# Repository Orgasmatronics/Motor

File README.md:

### Motor

This is a modular system for manufacturing motors scalably from the waste streams of consumer capitalism.   

The system consists of:

1. a control board
2. drive and pickup coils
3. energy storage
4. mechanical-to-electrical energy conversion circuits
4. modular mechanical framing system
5. mechanical oscillators(mass + spring)
6. bearings, shafts and drive trains
7. IoT interface

Taken together, the components of this system should be usable to construct machines that can automate the manufacture of more components of the system, creating the ability to self-propagate.  

As of now(November 2015) there are several parts that have to be either bought or made with commercial tools like the 3d printer.  A ongoing goal of this project is to replace all those components so that the whole project can be re-created from scratch using waste streams _only_.

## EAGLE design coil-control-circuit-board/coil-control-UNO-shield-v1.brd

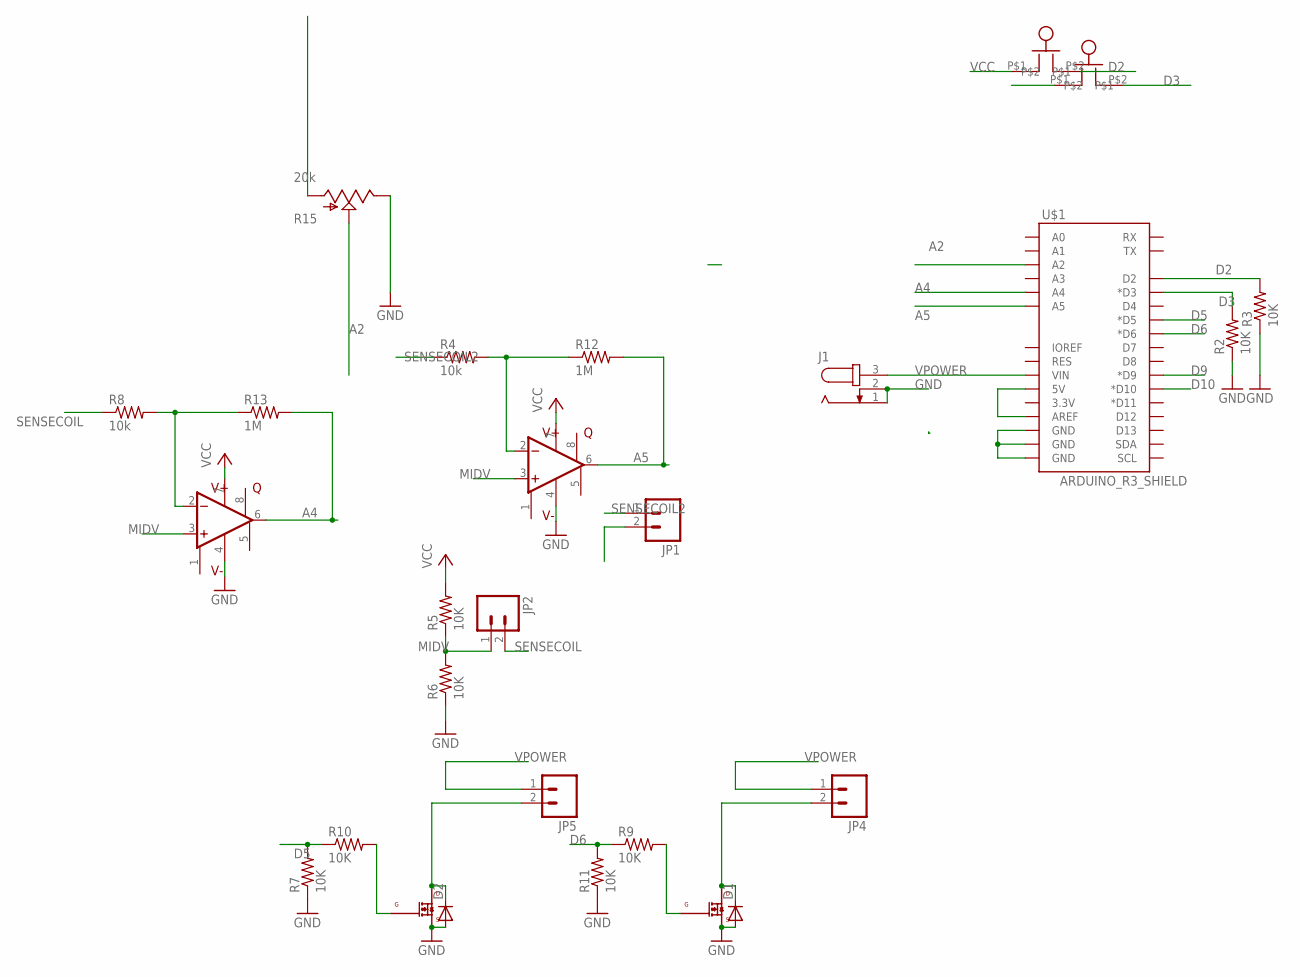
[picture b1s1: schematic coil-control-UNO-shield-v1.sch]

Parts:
D1, D2: DIODE-DO-214AC; DO-214AC
J1: JACK-PLUG1; SPC4078
JP1, JP2, JP4, JP5: M02PTH; 1X02
Q1, Q2: IRLML0060; SOT-23
R2, R3, R5, R6, R7, R9, R10, R11: 10K; R0603
R4, R8: 10k; 0603-RES
R12, R13: 1M; 0805
R15: 20k; ALPS_POT_KIT
SW2, SW3: BUTTON
U2, U3: LM4250; DIP08
U$1: ARDUINO_R3_SHIELD; UNO_R3_SHIELD

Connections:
A2: R15.P$2 (S), U$1.A2
A4: R13.2, U2.6 (OUT), U$1.A4
A5: R12.2, U3.6 (OUT), U$1.A5
D2: R3.2, SW2.P$2, U$1.D2
D3: R2.2, SW3.P$2, U$1.D3 (*D3)
D5: R7.2, R10.1, U$1.D5 (*D5)
D6: R9.1, R11.2, U$1.D6 (*D6)
D9: U$1.D9 (*D9)
D10: U$1.D10 (*D10)
GND: D1.A, D2.A, J1.1, J1.2, Q1.2 (SOURCE), Q2.2 (SOURCE), R2.1, R3.1, R6.1, R7.1, R11.1, R15.P$1 (E), U2.4 (V-), U3.4 (V-), U$1.GND@0 (GND), U$1.GND@1 (GND), U$1.GND@2 (GND)
MIDV: JP1.2, JP2.1, R5.1, R6.2, U2.3 (+IN), U3.3 (+IN)
unnamed: R4.2, R12.1, U3.2 (-IN)
unnamed: Q1.1 (GATE), R9.2
unnamed: R8.2, R13.1, U2.2 (-IN)
unnamed: D1.C, JP4.2, Q1.3 (DRAIN)
unnamed: Q2.1 (GATE), R10.2
unnamed: D2.C, JP5.2, Q2.3 (DRAIN)
SENSECOIL: JP2.2, R8.1
SENSECOIL2: JP1.1, R4.1
VCC: R5.2, R15.P$3 (A), SW2.P$1, SW3.P$1, U2.7 (V+), U3.7 (V+), U$1.5V, U$1.AREF
VPOWER: J1.3, JP4.1, JP5.1, U$1.VIN

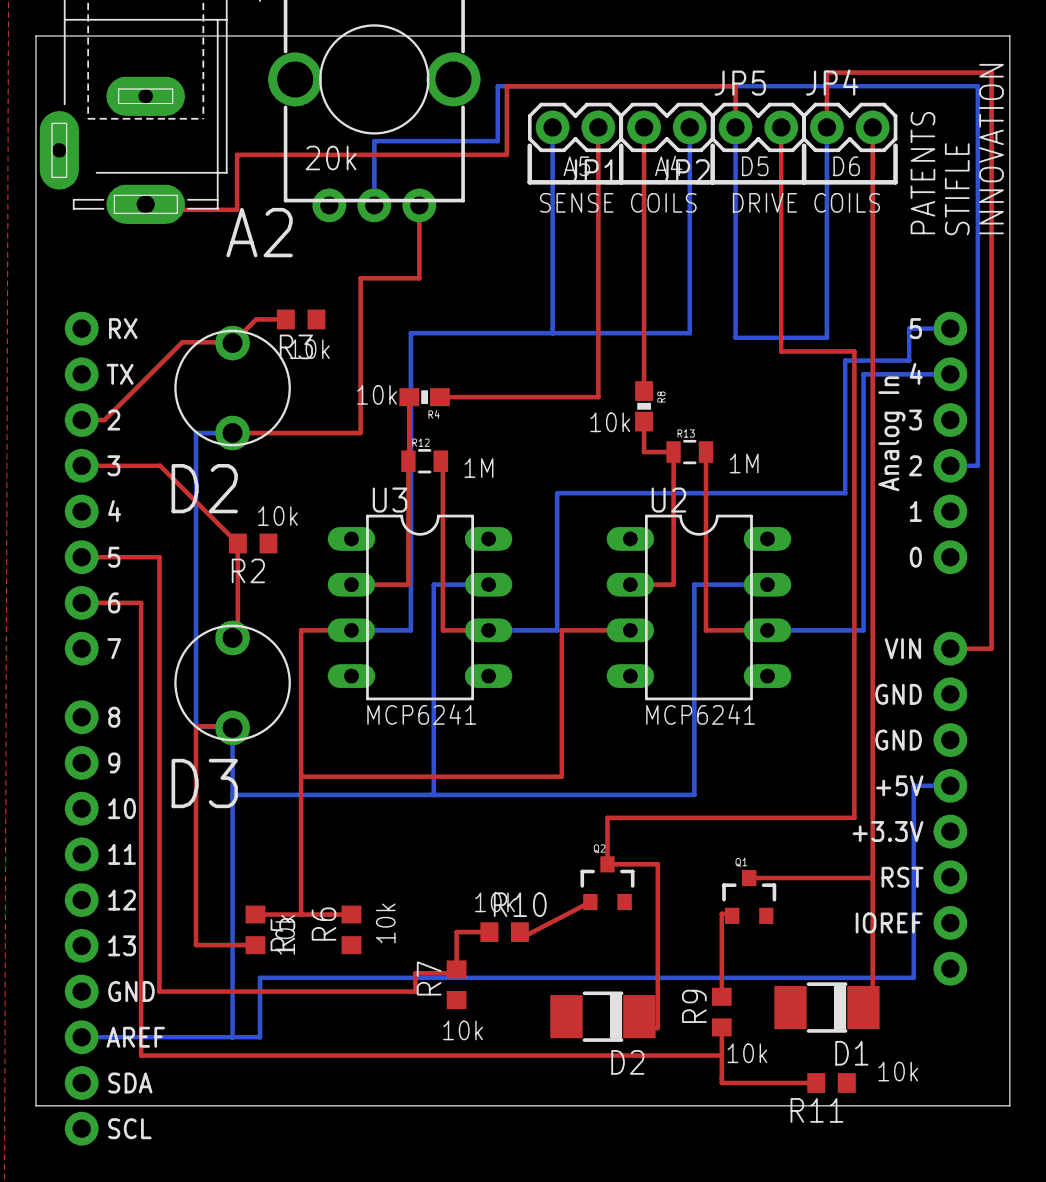
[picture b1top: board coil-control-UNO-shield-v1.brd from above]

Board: 2 copper layers, 54.1 x 59.4 mm, 27 parts (0 on the bottom side), 19 nets.

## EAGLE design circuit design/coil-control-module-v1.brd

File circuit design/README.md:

version 3: assembled fall 2015, used all through october and november

version 4: finishing it up late november, assembly planned soon

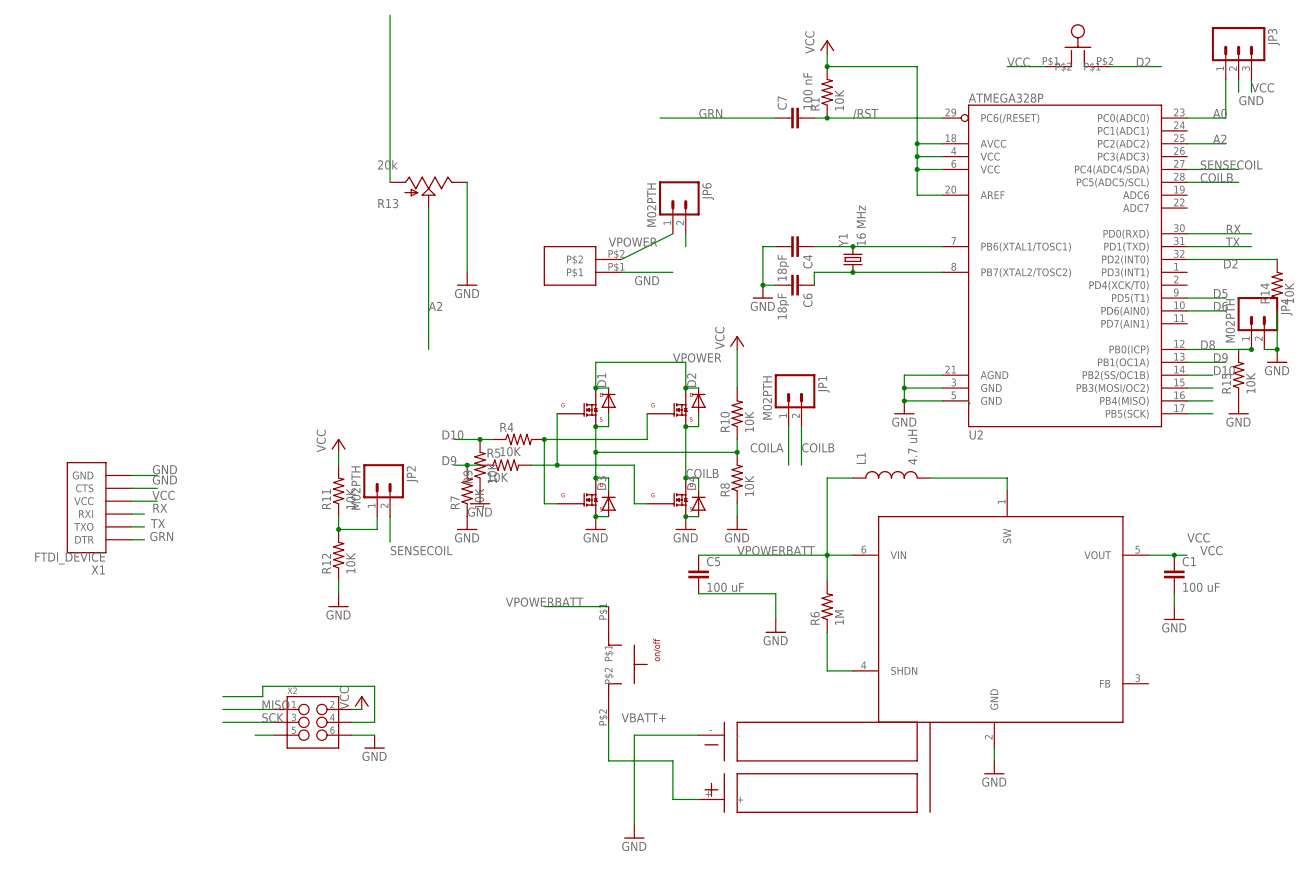
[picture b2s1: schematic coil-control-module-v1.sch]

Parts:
C1, C5: 100 uF; 1206
C4, C6: 18pF; C0603
C7: 100 nF; 0603-CAP
D1, D2, D3, D4: DIODE-DO-214AC; DO-214AC
JP1, JP2, JP4, JP6: M02PTH; 1X02
JP3: M03PTH; 1X03
L1: 4.7 uH; 0805
R1, R4, R5, R7, R8, R9, R10, R11, R12, R14, R15: 10K; R0603
R6: 1M; 0805
R13: 20k; ALPS_POT_KIT
U1: AAT1217; SSOT23-6
U2: ATMEGA328P; TQFP32-08
U$1, U$2, U$3, U$6: IRLML0060; SOT-23
U$4: AA-DOUBLE-UPSIDE-DOWN
U$5: CW182-ND
U$7: BUTTON
U$8: SPRING-TERMINAL
X1: FTDI_DEVICE; FTDI_DEVICE_SIDE
X2: M03X2NO_SILK; 2X3-NS
Y1: 16 MHz; CRYSTAL-SMD-5X3

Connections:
/RST: C7.2, R1.1, U2.29 (PC6(/RESET)), X2.5
A0: JP3.1, U2.23 (PC0(ADC0))
A2: R13.P$2 (S), U2.25 (PC2(ADC2))
COILA: D1.A, D3.C, JP1.1, R8.2, R10.1, U$3.2 (SOURCE), U$6.3 (DRAIN)
COILB: D2.A, D4.C, JP1.2, U2.28 (PC5(ADC5/SCL)), U$1.3 (DRAIN), U$2.2 (SOURCE)
D2: R14.2, U2.32 (PD2(INT0)), U$7.P$2
D5: U2.9 (PD5(T1))
D6: U2.10 (PD6(AIN0))
D8: JP4.1, R15.2, U2.12 (PB0(ICP))
D9: R5.1, R7.2, U2.13 (PB1(OC1A))
D10: R4.1, R9.2, U2.14 (PB2(SS/OC1B))
GND: C1.2, C4.2, C5.2, C6.2, D3.A, D4.A, JP3.2, JP4.2, R7.1, R8.1, R9.1, R12.1, R13.P$1 (E), R14.1, R15.1, U1.2 (GND), U2.3 (GND), U2.5 (GND), U2.21 (AGND), U$1.2 (SOURCE), U$4.-, U$6.2 (SOURCE), U$8.P$1, X1.P$5 (CTS), X1.P$6 (GND), X2.6
GRN: C7.1, X1.P$1 (DTR)
MISO: U2.16 (PB4(MISO)), X2.1
MOSI: U2.15 (PB3(MOSI/OC2)), X2.4
unnamed: C4.1, U2.7 (PB6(XTAL1/TOSC1)), Y1.3 (2)
unnamed: C6.1, U2.8 (PB7(XTAL2/TOSC2)), Y1.1
unnamed: JP2.1, R11.1, R12.2
unnamed: L1.2, U1.1 (SW)
unnamed: R5.2, U$1.1 (GATE), U$3.1 (GATE)
unnamed: R4.2, U$2.1 (GATE), U$6.1 (GATE)
RX: U2.30 (PD0(RXD)), X1.P$3 (RXI)
SCK: U2.17 (PB5(SCK)), X2.3
SENSECOIL: JP2.2, U2.27 (PC4(ADC4/SDA))
SHDN: R6.1, U1.4 (SHDN)
TX: U2.31 (PD1(TXD)), X1.P$2 (TXO)
VBATT+: U$4.+, U$5.P$2
VCC: C1.1, JP3.3, R1.2, R10.2, R11.2, R13.P$3 (A), U1.5 (VOUT), U2.4 (VCC), U2.6 (VCC), U2.18 (AVCC), U2.20 (AREF), U$7.P$1, X1.P$4 (VCC), X2.2
VPOWER: D1.C, D2.C, JP6.1, U$2.3 (DRAIN), U$3.3 (DRAIN), U$8.P$2
VPOWERBATT: C5.1, JP6.2, L1.1, R6.2, U1.6 (VIN), U$5.P$1

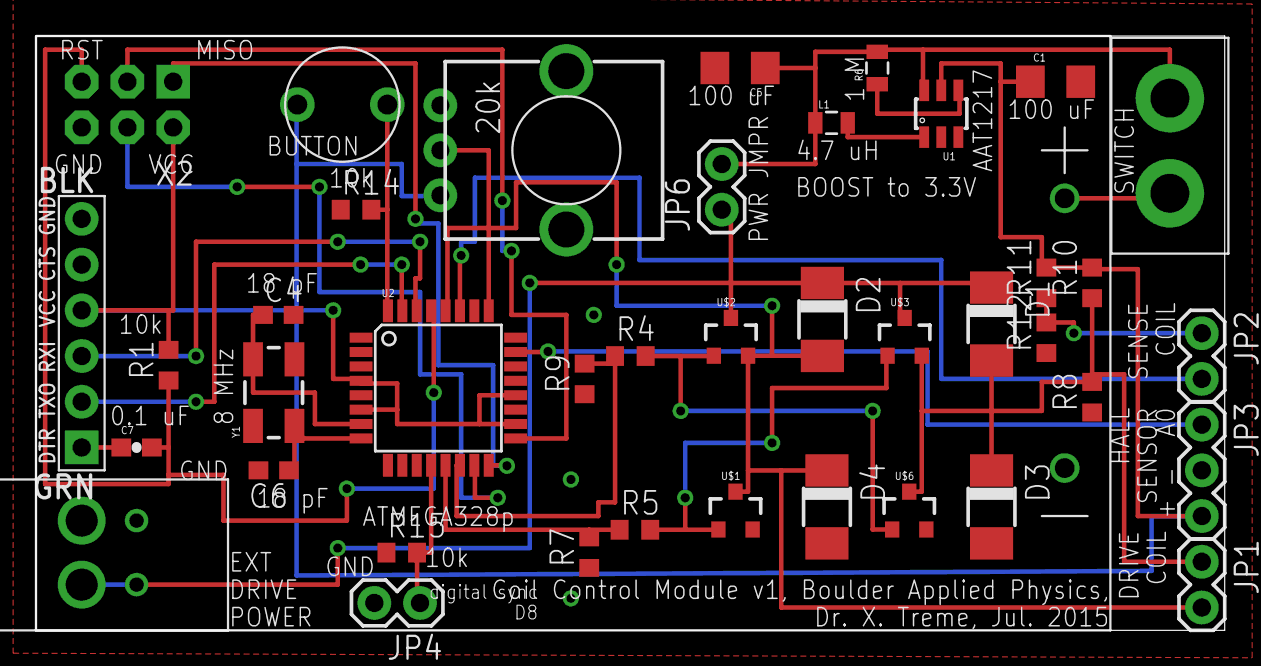
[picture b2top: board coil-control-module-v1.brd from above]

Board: 2 copper layers, 66.0 x 33.0 mm, 41 parts (0 on the bottom side), 28 nets.

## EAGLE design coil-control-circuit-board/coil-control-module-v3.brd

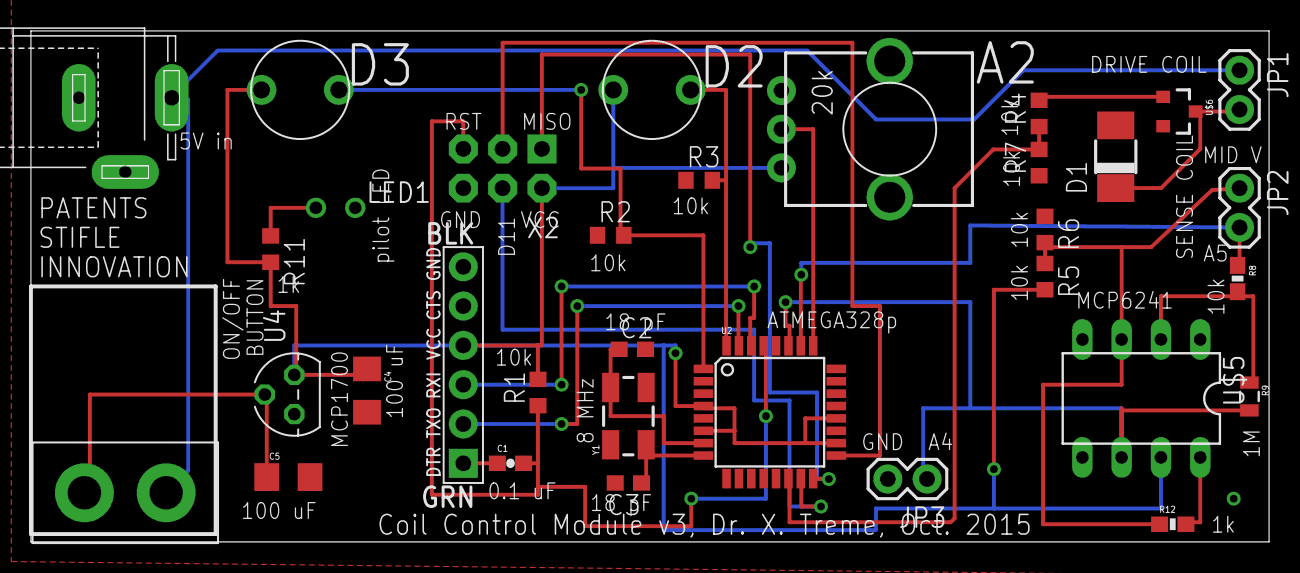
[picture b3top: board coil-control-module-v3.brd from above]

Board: 2 copper layers, 80.0 x 33.0 mm, 33 parts (0 on the bottom side), 25 nets.

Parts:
C1: 100 nF; 0603-CAP
C2, C3: 18pF; C0603
C4, C5: 100 uF; 1206
D1: DO-214AC
J1: SPC4078
JP1, JP2, JP3: 1X02
LED1: LED3MM-NS
R1, R2, R3, R4, R5, R6, R7: 10K; R0603
R8: 10k; 0603-RES
R9: 1M; 0805
R10: 20k; ALPS_POT_KIT
R11: 3.3k; R0603
R12: 1k; 0603-RES
SW1: CW182-ND
SW2, SW3: BUTTON
U2: ATMEGA328P; TQFP32-08
U4: MCP1700; TO92-3
U$5: LM4250; DIP08
U$6: IRLML0060; SOT-23
X1: FTDI_DEVICE; FTDI_DEVICE_SIDE
X2: 2X3-NS
Y1: 16 MHz; CRYSTAL-SMD-5X3

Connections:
/RST: C1.2, R1.1, U2.29, X2.5
A2: R10.P$2, U2.25
A4: JP3.1, R9.2, U2.27, U$5.6
D2: R3.2, SW2.P$2, U2.32
D3: R2.2, SW3.P$2, U2.1
D10: R4.1, R7.2, U2.14
GND: C2.2, C3.2, C4.2, C5.2, D1.A, J1.1, J1.2, JP3.2, LED1.K, R2.1, R3.1, R6.1, R7.1, R10.P$1, U2.3, U2.5, U2.21, U4.1, U$5.4, U$6.2, X1.P$5, X1.P$6, X2.6
GRN: C1.1, X1.P$1
MIDV: JP2.1, R5.1, R6.2, R12.1, U$5.3
MISO: U2.16, X2.1
MOSI: U2.15, X2.4
unnamed: D1.C, JP1.2, U$6.3
unnamed: C2.1, U2.7, Y1.3
unnamed: LED1.A, R11.1
unnamed: C3.1, U2.8, Y1.1
unnamed: R8.2, R9.1, U$5.2
unnamed: R12.2, U$5.8
unnamed: R4.2, U$6.1
RX: U2.30, X1.P$3
SCK: U2.17, X2.3
SENSECOIL: JP2.2, R8.1, U2.26
TX: U2.31, X1.P$2
VCC: C4.1, R1.2, R5.2, R10.P$3, R11.2, SW2.P$1, SW3.P$1, U2.4, U2.6, U2.18, U2.20, U4.3, U$5.7, X1.P$4, X2.2
VIN: C5.1, SW1.P$2, U4.2
VPOWER: J1.3, JP1.1, SW1.P$1

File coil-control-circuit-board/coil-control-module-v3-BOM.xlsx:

REFDES | Value | QTY | Manufacturer | Manufacturer Part Number | Digikey Part Number | Package
Y1 | 8 MHz | 1 | TXC Corp | 7B-8.000MAAJ-T | 887-1452-1-ND | 4-SMD
Q1 | MOSFET | 1 | International Rectifier | IRLML0060TRPBF | IRLML0060TRPBFCT-ND | SOT-23
U1 | ATMEGA328p | 1 | Atmel | ATMEGA328-AU | ATMEGA328-AU-ND | 32TQFP
U2 | op amp | 1 | Microchip | MCP6241-E/P | MCP6241-E/P-ND | 8-DIP
U3 | socket | 1 | assmann | A08-LC-TT | AE9986-ND | 8-DIP
U4 | 3.3 V regulator | 1 | Microchip | MCP1700-3302E/TO | MCP1700-3302E/TO-ND | TO-92-3
D1 | diode | 1 | Fairchild Semiconductor | S1B | S1BFSCT-ND | DO-214AC
LED1 | green | 1 | KingBright | WP7113GT | 754-1731-ND
C1 | 100 nF | 1 | Yageo | CC0603KRX7R8BB104 | 311-1341-1-ND | "0603"
C2 | 18 pF | 2 | Yageo | CC0603JRNPO9BN180 | 311-1061-1-ND | "0603"
C3 | 18 pF |  | Yageo | CC0603JRNPO9BN180 | 311-1061-1-ND | "0603"
C4 | 100 uF | 2 | Murata | GRM31CE70G107ME39L | 490-9966-1-ND | "1206"
C5 | 100 uF |  | Murata | GRM31CE70G107ME39L | 490-9966-1-ND | "1206"
R1 | 10k | 8 | panasonic | ERJ-3EKF1002V | P10.0KHCT-ND | "0603"
R2 | 10k |  | panasonic | ERJ-3EKF1002V | P10.0KHCT-ND | "0603"
R3 | 10k |  | panasonic | ERJ-3EKF1002V | P10.0KHCT-ND | "0603"
R4 | 10k |  | panasonic | ERJ-3EKF1002V | P10.0KHCT-ND | "0603"
R5 | 10k |  | panasonic | ERJ-3EKF1002V | P10.0KHCT-ND | "0603"
R6 | 10k |  | panasonic | ERJ-3EKF1002V | P10.0KHCT-ND | "0603"
R7 | 10k |  | panasonic | ERJ-3EKF1002V | P10.0KHCT-ND | "0603"
R8 | 10k |  | panasonic | ERJ-3EKF1002V | P10.0KHCT-ND | "0603"
R9 | 1M | 1 | Panasonic Electronic Components | ERJ-6ENF1004V | P1.00MCCT-ND | "0805"
R10 | 20k pot | 1 | Bourns | PTV09A-4030U-B203 | PTV09A-4030U-B203-ND
R11 | 3.3k | 1 | Panasonic Electronic Components | ERJ-3EKF3301V | P3.30KHCT-ND | "0603"
R12 | 1k | 1 | Panasonic Electronic Components | ERJ-3EKF1001V | P1.00KHCT-ND | "0603"
SW1 | on/off | 1 | CW industries | GPTS203211B | CW181-ND
SW2 | button | 2 | Panasonic | EVQ-11U05R | P8083SCT-ND
SW3 | button |  | Panasonic | EVQ-11U05R | P8083SCT-ND
J1 | power socket | 1 | CUI, inc | PJ-102AH | CP-102AH-ND
X1 | 1X6 pin header | 1 | samtec | TSW-106-14-G-S
X2 | 1X2 pin header | 2 | samtec | TSW-102-14-G-S
X3 |  |  | samtec | TSW-102-14-G-S
W1 | 2 wire samtec cable | 2 | samtec | IDSS-02-D-10.00
W2 | 2 wire samtec cable |  | samtec | IDSS-02-D-10.00

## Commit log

2015-09-02 Basic pulse driver
    dumb(no dynamic tracking, no data taking) periodic pulses, tuned with knob
2015-09-02 Rename pulseDriver2 to pulseDriver2.ino
2015-09-02 added comments and description
2015-09-02 Simple button control
    Very simple but important program for debugging: control current through the coil using the button.
2015-09-02 Pulse Data Button
    when button is pressed, a pulse is applied to the coil, data are recorded and sent down the serial line.
2015-09-02 Python plots of pulseDataButton
    python plotter(non-GUI) to go with pulseDataButton
2015-09-02 moved code to end, added "license"
2015-10-12 Generic drive with 3 modes for coil
    kind of stable now, will probably keep this code for a few weeks of hardware work, then probably tweak, messing with the thresholds of the feedback triggers
2015-11-06 two mode, standardized data
    data are now sent down serial port in form expected by Arduino serial plotter and the dumb frequency drive is eliminated, so it's either push-button drive or feedback drive.
2015-11-06 fixed killed vars
    killed emdead
2015-11-13 added off
2015-11-13 Update and rename unified-controller1 to unified-controller1.ino
    added outputs on pin 11 so that a second coil can be controlled with a second board
2015-11-21 a
    a
2015-11-22 uploading the last few months of circuits
    finally trying to use github correctly, uploading a bunch of files from
    the lest few months
2015-11-22 Create read-me
2015-11-22 testing markdown latex
2015-11-22 change name of directory with all the circuit designs in it
2015-11-22 added 3d files for drive and sense coil
2015-11-22 change file names to be more explanatory
2015-11-22 Create README.md.
    describe the 3d files
2015-11-22 clean up files in motor directory
2015-11-22 more cleanup, moved arduino code files together
2015-11-22 added python theory notebooks
2015-11-22 Rename README.md. to README.md
2015-11-22 create UNO shield version of v4 board
    …which is v1 now because the shield is a separate thing
2015-11-22 finished the boards, mostly
    added DC power connector, shifted everything over to work on the Yun(
    make space for the big connectors), connected Vin to the input DC
    power, cleaned stuff up a bit, moved stuff around.
2015-11-22 added BOM for shield board
    and also tweaked board file a bit
2015-11-22 added zipped gerber files
    files to send to PCB fab house, generated from Eagle using the spark
    fun job
2015-11-26 added theory on feedback drive
2015-11-27 adding random figures to test image embed
2015-11-27 adding random images to figure out embedding code
2015-11-27 drive coil docs, theory
2015-11-28 adding to drive coil documentation
2015-11-28 Rename Drive Coil Doc.ipynb to Drive_Coil_Doc.ipynb
2015-11-29 very crude L/R calculations
    very very crude, need better analysis!
2015-11-30 measure inductance with mbk
    very very rough, still need real documentation and better data. Looks
    like inductance of drive coil is about 1 mH as I would expect from rough
    solenoid calculations.
2015-11-30 move files around
2015-12-02 documenting inductance measurement methods
2015-12-02 working on inductance measurement code
2015-12-03 more data taking on L/R time measurement
    changed the arduino code to make it cleaner and faster, took some nicer
    plots, plotted residuals, saved some data in npy format
2015-12-03 putting together blog data
    more data plotting for documentation on blog
2015-12-08 blah blah blah
2015-12-30 stuff
2016-01-01 moarstuffslozl
2016-01-02 edits

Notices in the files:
parts and their libraries:
SparkFun-FreqCtrl: Licensing: Creative Commons ShareAlike 4.0 International - https://creativecommons.org/licenses/by-sa/4.0
SparkFun-Passives: Licensing: CC v3.0 Share-Alike You are welcome to use this library for commercial purposes.
